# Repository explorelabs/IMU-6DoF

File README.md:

IMU-6DoF
========

A Breakout Board for Invensense's MPU-6050, a Six-Axis (Gyro + Accelerometer) MEMS Device.

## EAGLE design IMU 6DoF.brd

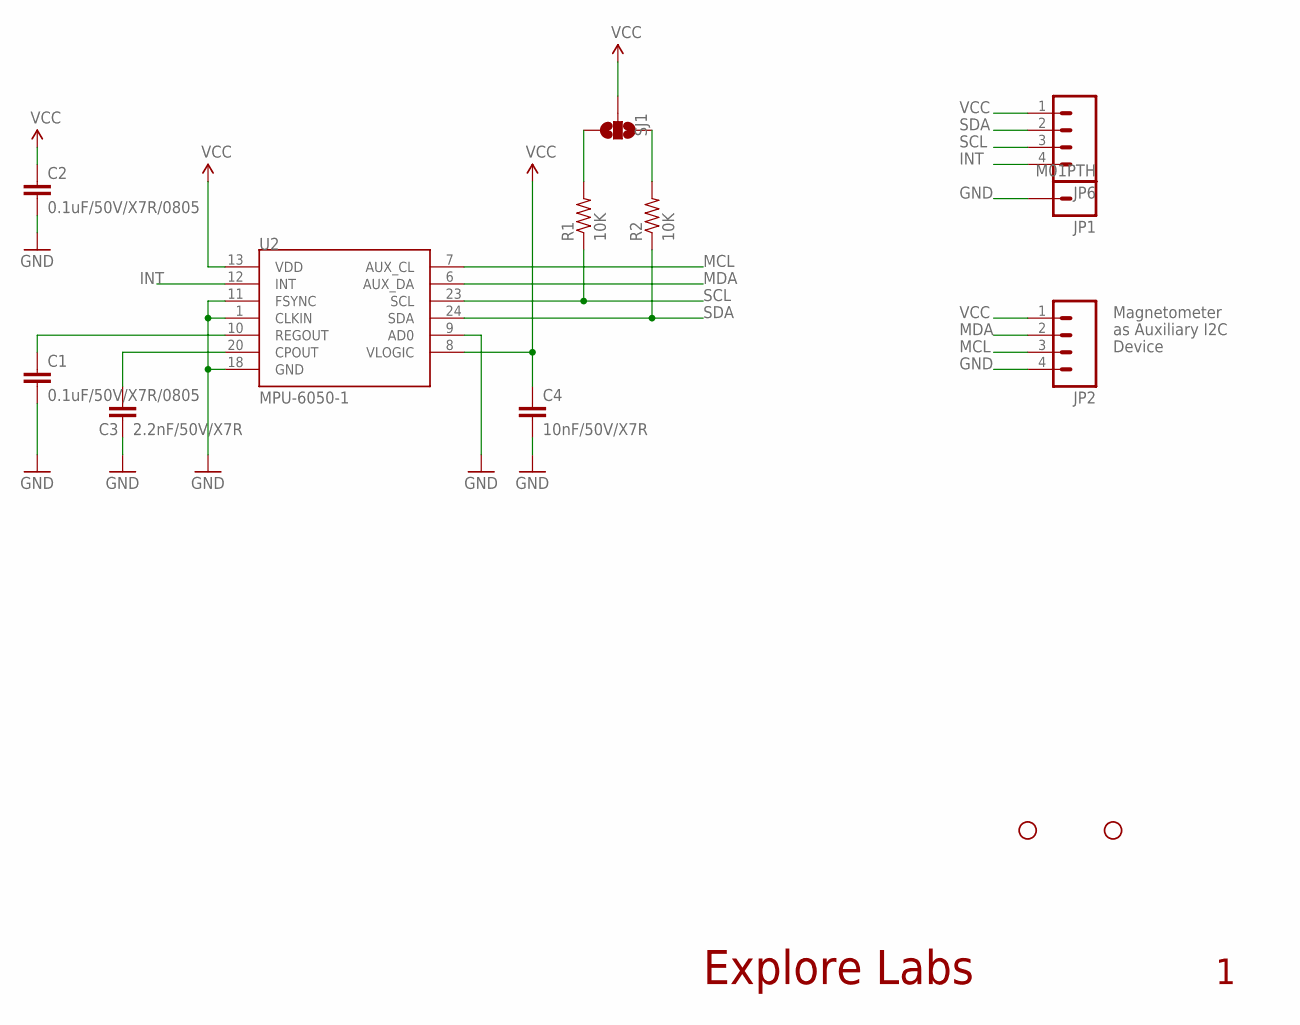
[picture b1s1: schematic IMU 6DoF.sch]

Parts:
C1, C2: 0.1uF/50V/X7R/0805; 0805
C3: 2.2nF/50V/X7R; 0805
C4: 10nF/50V/X7R; 0805
JP1: M01PTH; 1X01
JP2, JP6: M04PTH; 1X04
JP3, JP4: STAND-OFFTIGHT; STAND-OFF-TIGHT
R1, R2: 10K; 0603-RES
SJ1: SOLDERJUMPER_2WAYT; SJ_2
U2: MPU-6050-1; QFN-24-4MM2

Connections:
GND: C1.2, C2.2, C3.2, C4.2, JP1.1, JP2.4, U2.1 (CLKIN), U2.9 (AD0), U2.11 (FSYNC), U2.18 (GND)
INT: JP6.4, U2.12 (INT)
MCL: JP2.3, U2.7 (AUX_CL)
MDA: JP2.2, U2.6 (AUX_DA)
unnamed: C3.1, U2.20 (CPOUT)
unnamed: C1.1, U2.10 (REGOUT)
unnamed: R1.2, SJ1.3
unnamed: R2.2, SJ1.1
SCL: JP6.3, R1.1, U2.23 (SCL)
SDA: JP6.2, R2.1, U2.24 (SDA)
VCC: C2.1, C4.1, JP2.1, JP6.1, SJ1.2, U2.8 (VLOGIC), U2.13 (VDD)

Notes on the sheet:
Explore Labs
Magnetometer
as Auxiliary I2C
Device

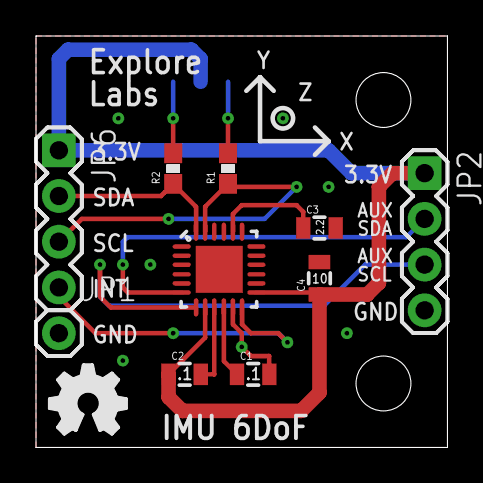
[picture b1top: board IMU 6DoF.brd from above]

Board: 2 copper layers, 22.9 x 22.9 mm, 14 parts (1 on the bottom side), 11 nets.

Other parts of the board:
LOGO1: OSHW_LOGO_FILLX0150-NT; OSHW_FILLX150_NOTEXT

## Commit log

2012-11-23 Gerber Data and Board & Sch files for IMU 6DoF
2013-01-08 added schematic in PDF format
2013-05-04 moved silkscreen file to root
    .silk

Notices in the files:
parts and their libraries:
SparkFun-Passives: Licensing: CC v3.0 Share-Alike You are welcome to use this library for commercial purposes.
SparkFun-Aesthetics: Released under the Creative Commons
SparkFun-Aesthetics: http://creativecommons.org/licenses/by-sa/3.0
